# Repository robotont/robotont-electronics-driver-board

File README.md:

# robotont-electronics-driver-board
The repository contains KiCAD schematics and PCB layout for the motor driver board.
The [production](Production/) folder contains prepared gerbers with pos file ready to order a from e.g. JLCPCB.

## Schematics

## Layout

The following figures visualize the front and back side of the driver board along with the 3D model of the design.

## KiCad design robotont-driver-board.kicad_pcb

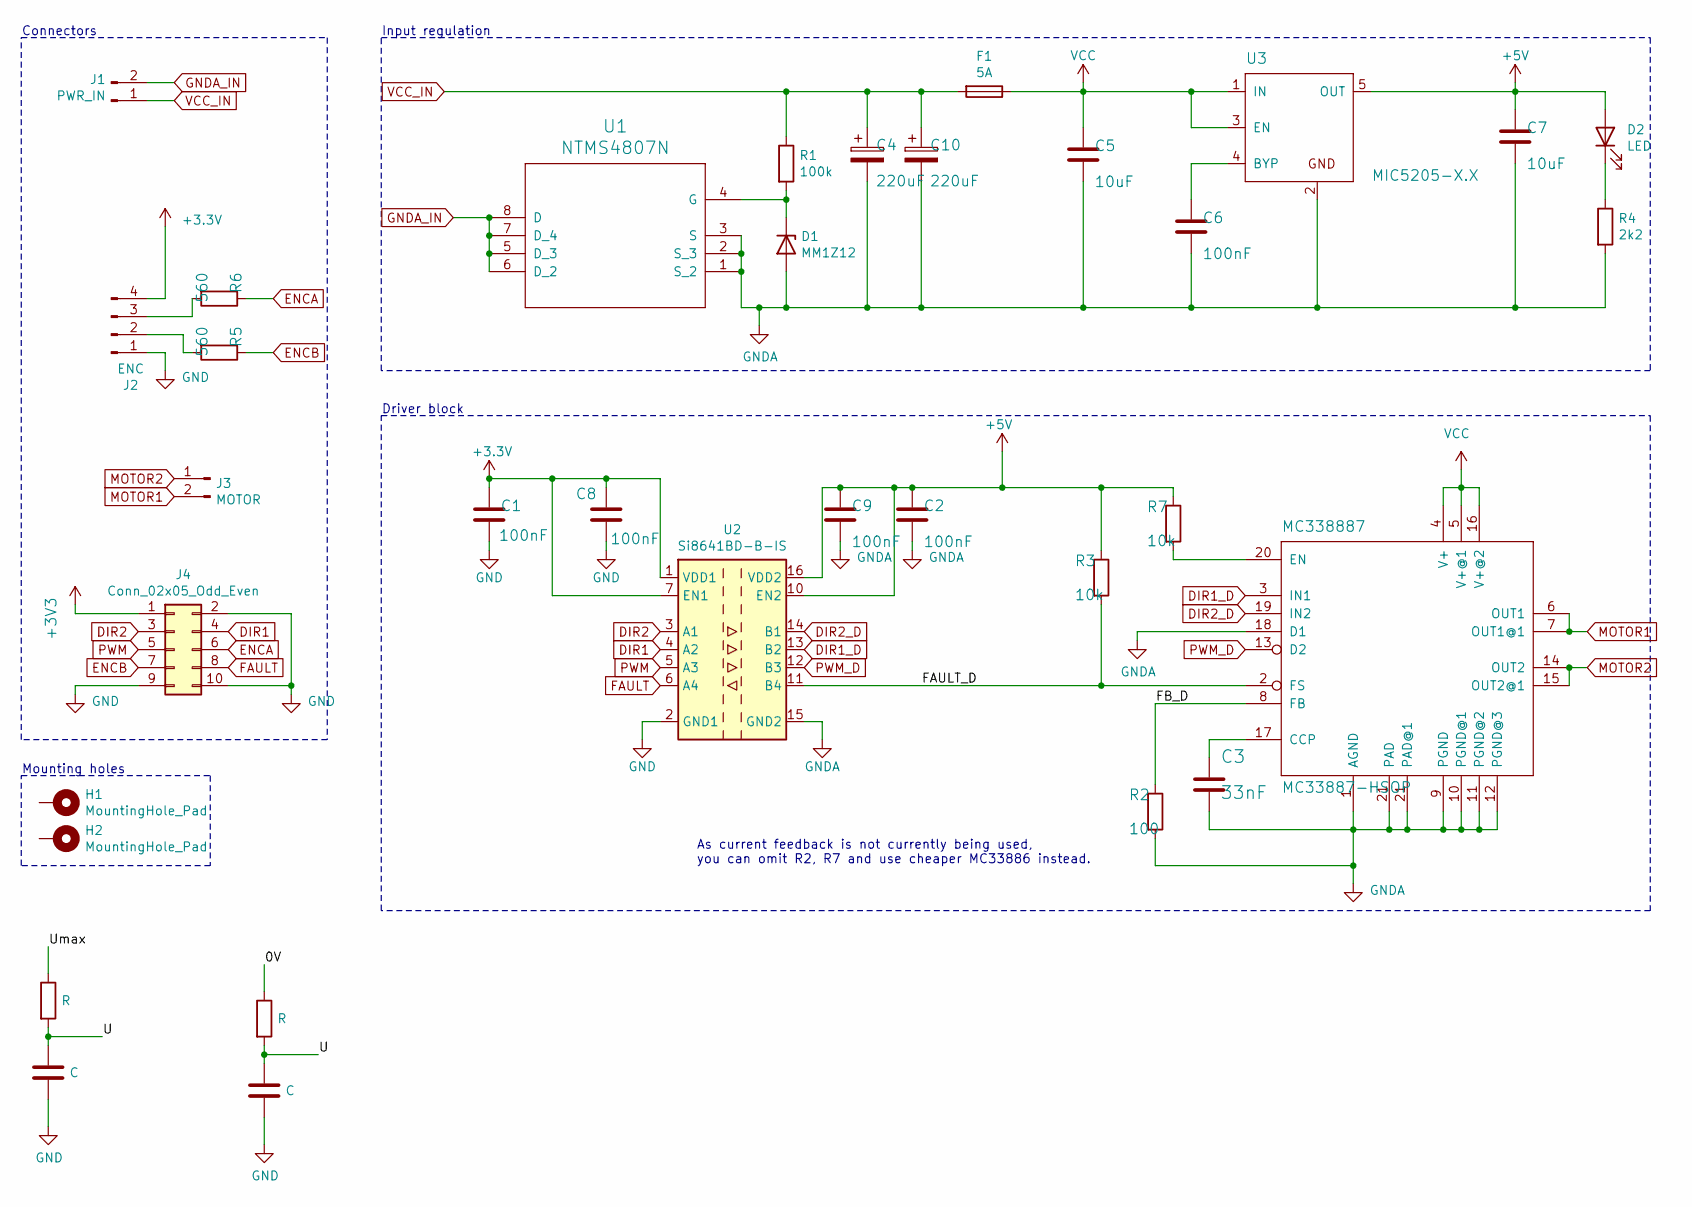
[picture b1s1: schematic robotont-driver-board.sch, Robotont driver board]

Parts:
C1, C2, C6, C8, C9: 100nF; C_0603_1608Metric; LCSC # C14663
C3: 33nF; C_0603_1608Metric; LCSC # C21117
C4, C10: 220uF; CP_Radial_D8.0mm_P3.50mm
C5, C7: 10uF; C_1206_3216Metric; LCSC # C13585
D1: MM1Z12; D_SOD-123; LCSC # C115273
D2: LED; LED_0603_1608Metric; LCSC # C72043
F1: 5A; Fuse_1206_3216Metric; LCSC # C182976
H1, H2: MountingHole_Pad; MountingHole_3mm_Pad
J1: PWR_IN; KF2510-2AWG
J2: ENC; JST_XH_S4B-XH-A_1x04_P2.50mm_Horizontal
J3: MOTOR; JST_XH_S2B-XH-A_1x02_P2.50mm_Horizontal
J4: Conn_02x05_Odd_Even; CONN-TE-MICROMATCH-5X2-PTH-BOSS
MC338887: MC33887-HSOP; HSOP-20-1EP_11.0x15.9mm_P1.27mm_SlugDown_ThermalVias
R1: 100k; R_0603_1608Metric; LCSC # C25803
R2: 100; R_0603_1608Metric; LCSC # C22775
R3, R7: 10k; R_0603_1608Metric; LCSC # C25804
R4: 2k2; R_0603_1608Metric; LCSC # C4190
R5, R6: 560; R_0603_1608Metric; LCSC # C23204
U1: NTMS4807N; SO-8_3.9x4.9mm_P1.27mm; LCSC # C80851
U2: Si8641BD-B-IS; SOIC-16W_7.5x10.3mm_P1.27mm; LCSC # C461891
U3: MIC5205-X.X; SOT-23-5; LCSC # C70431

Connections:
+5V: C2.1, C7.1, C9.1, D2.2 (A), R3.1, R7.1, U2.10 (EN2), U2.16 (VDD2), U3.5 (OUT)
/FAULT_D: MC338887.2 (FS), R3.2, U2.11 (B4)
/FB_D: MC338887.8 (FB), R2.1
DIR1: J4.4, U2.4 (A2)
DIR1_D: MC338887.3 (IN1), U2.13 (B2)
DIR2: J4.3, U2.3 (A1)
DIR2_D: MC338887.19 (IN2), U2.14 (B1)
ENCA: J4.6, R6.1
ENCB: J4.7, R5.1
FAULT: J4.8, U2.6 (A4)
GND: C1.2, C8.1, J2.1, J4.2, J4.9, J4.10, U2.2 (GND1), U2.8 (GND1)
GNDA: C2.2, C3.2, C4.2, C5.2, C6.2, C7.2, C9.2, C10.2, D1.2 (A), MC338887.1 (AGND), MC338887.9 (PGND), MC338887.10 (PGND@1), MC338887.11 (PGND@2), MC338887.12 (PGND@3), MC338887.18 (D1), MC338887.21 (PAD), R2.2, R4.2, U1.1 (S_2), U1.2 (S_3), U1.3 (S), U2.9 (GND2), U2.15 (GND2), U3.2 (GND)
GNDA_IN: J1.2, U1.5 (D_3), U1.6 (D_2), U1.7 (D_4), U1.8 (D)
MOTOR1: J3.2, MC338887.6 (OUT1), MC338887.7 (OUT1@1)
MOTOR2: J3.1, MC338887.14 (OUT2), MC338887.15 (OUT2@1)
unnamed: C3.1, MC338887.17 (CCP)
unnamed: C6.1, U3.4 (BYP)
unnamed: D1.1 (K), R1.2, U1.4 (G)
unnamed: D2.1 (K), R4.1
unnamed: J2.2, R5.2
unnamed: J2.3, R6.2
unnamed: MC338887.20 (EN), R7.2
PWM: J4.5, U2.5 (A3)
PWM_D: MC338887.13 (D2), U2.12 (B3)
VCC: C5.1, F1.1, MC338887.4 (V+), MC338887.5 (V+@1), MC338887.16 (V+@2), U3.1 (IN), U3.3 (EN)
VCC_IN: C4.1, C10.1, F1.2, J1.1, R1.1

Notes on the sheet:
Connectors
Mounting holes
Input regulation
Driver block
As current feedback is not currently being used, you can omit R2, R7 and use cheaper MC33886 instead.

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
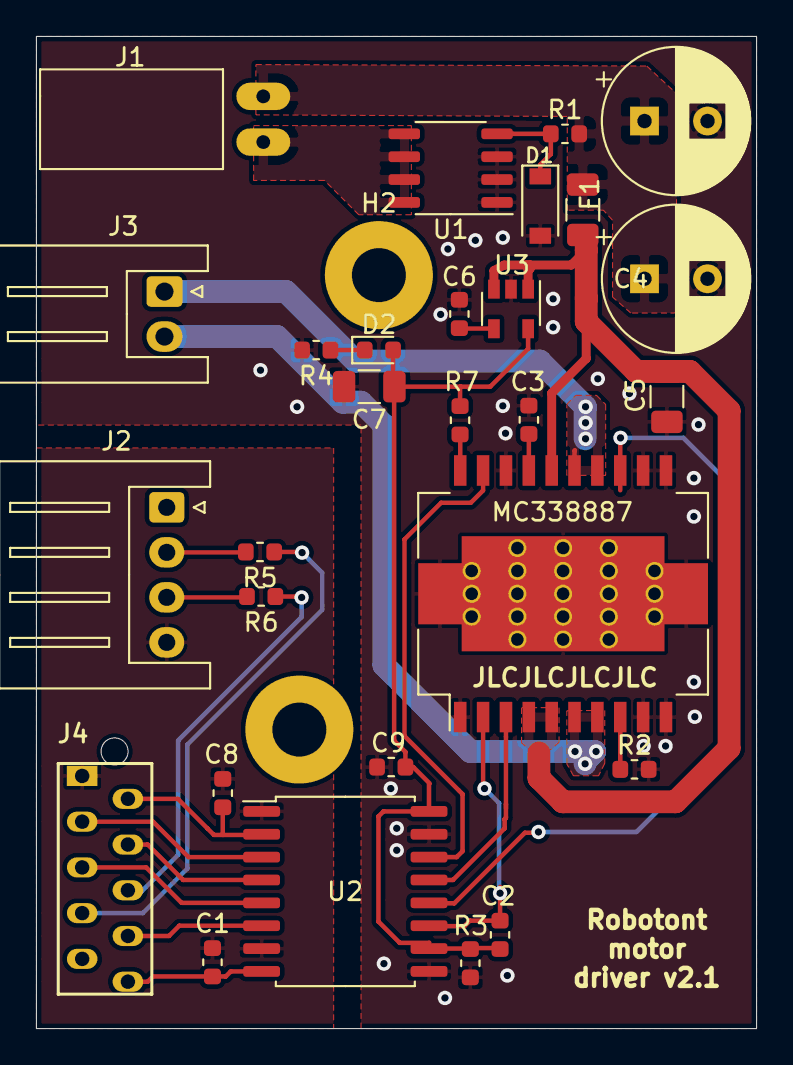
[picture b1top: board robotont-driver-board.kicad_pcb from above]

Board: 2 copper layers, 40.0 x 55.1 mm, 30 parts (0 on the bottom side), 27 nets.

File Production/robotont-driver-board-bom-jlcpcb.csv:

Comment,Designator,Footprint,LCSC Part #
33nF,C3,0603,C21117
10uF,"C5,C7",1206,C13585
100nF,"C1,C2,C8,C9",0603,C14663
MM1Z12,D1,SOD-123,C115273
LED,D2,0603,C72043
5A,F1,1206,C182976
100k,R1,0603,C25803
100,R2,0603,C22775
2k2,R4,0603,C4190
560,"R5,R6",0603,C23204
10k,"R7,R3",0603,C25804
NTMS4807N,U1,Package_SO:SO-8_3.9x4.9mm_P1.27mm,C80851
Si8641BD-B-IS,U2,Package_SO:SOIC-16W_7.5x10.3mm_P1.27mm,C461891
MIC5205-X.X,U3,Package_TO_SOT_SMD:SOT-23-5,C70431

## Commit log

2020-03-27 schematic converted from eagle
2020-03-31 v2.1 with jlcpcb components
2021-10-05 some cleanup, CERN permissive license, included jlcpcb position files
2022-08-26 added production files
2023-03-10 added some docs to readme
2023-03-10 fixed repo name in Readme

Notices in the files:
robotont-driver-board.sch:
Licensed under CERN-OHL-P
